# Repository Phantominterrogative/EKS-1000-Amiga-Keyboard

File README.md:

# EKS-1000-Amiga-Keyboard
A new PCB for those who like the Amiga A1000 keyboard.
This is an open source design. Feel free to download and import into KiCAD or EagleCAD for your own personal use.

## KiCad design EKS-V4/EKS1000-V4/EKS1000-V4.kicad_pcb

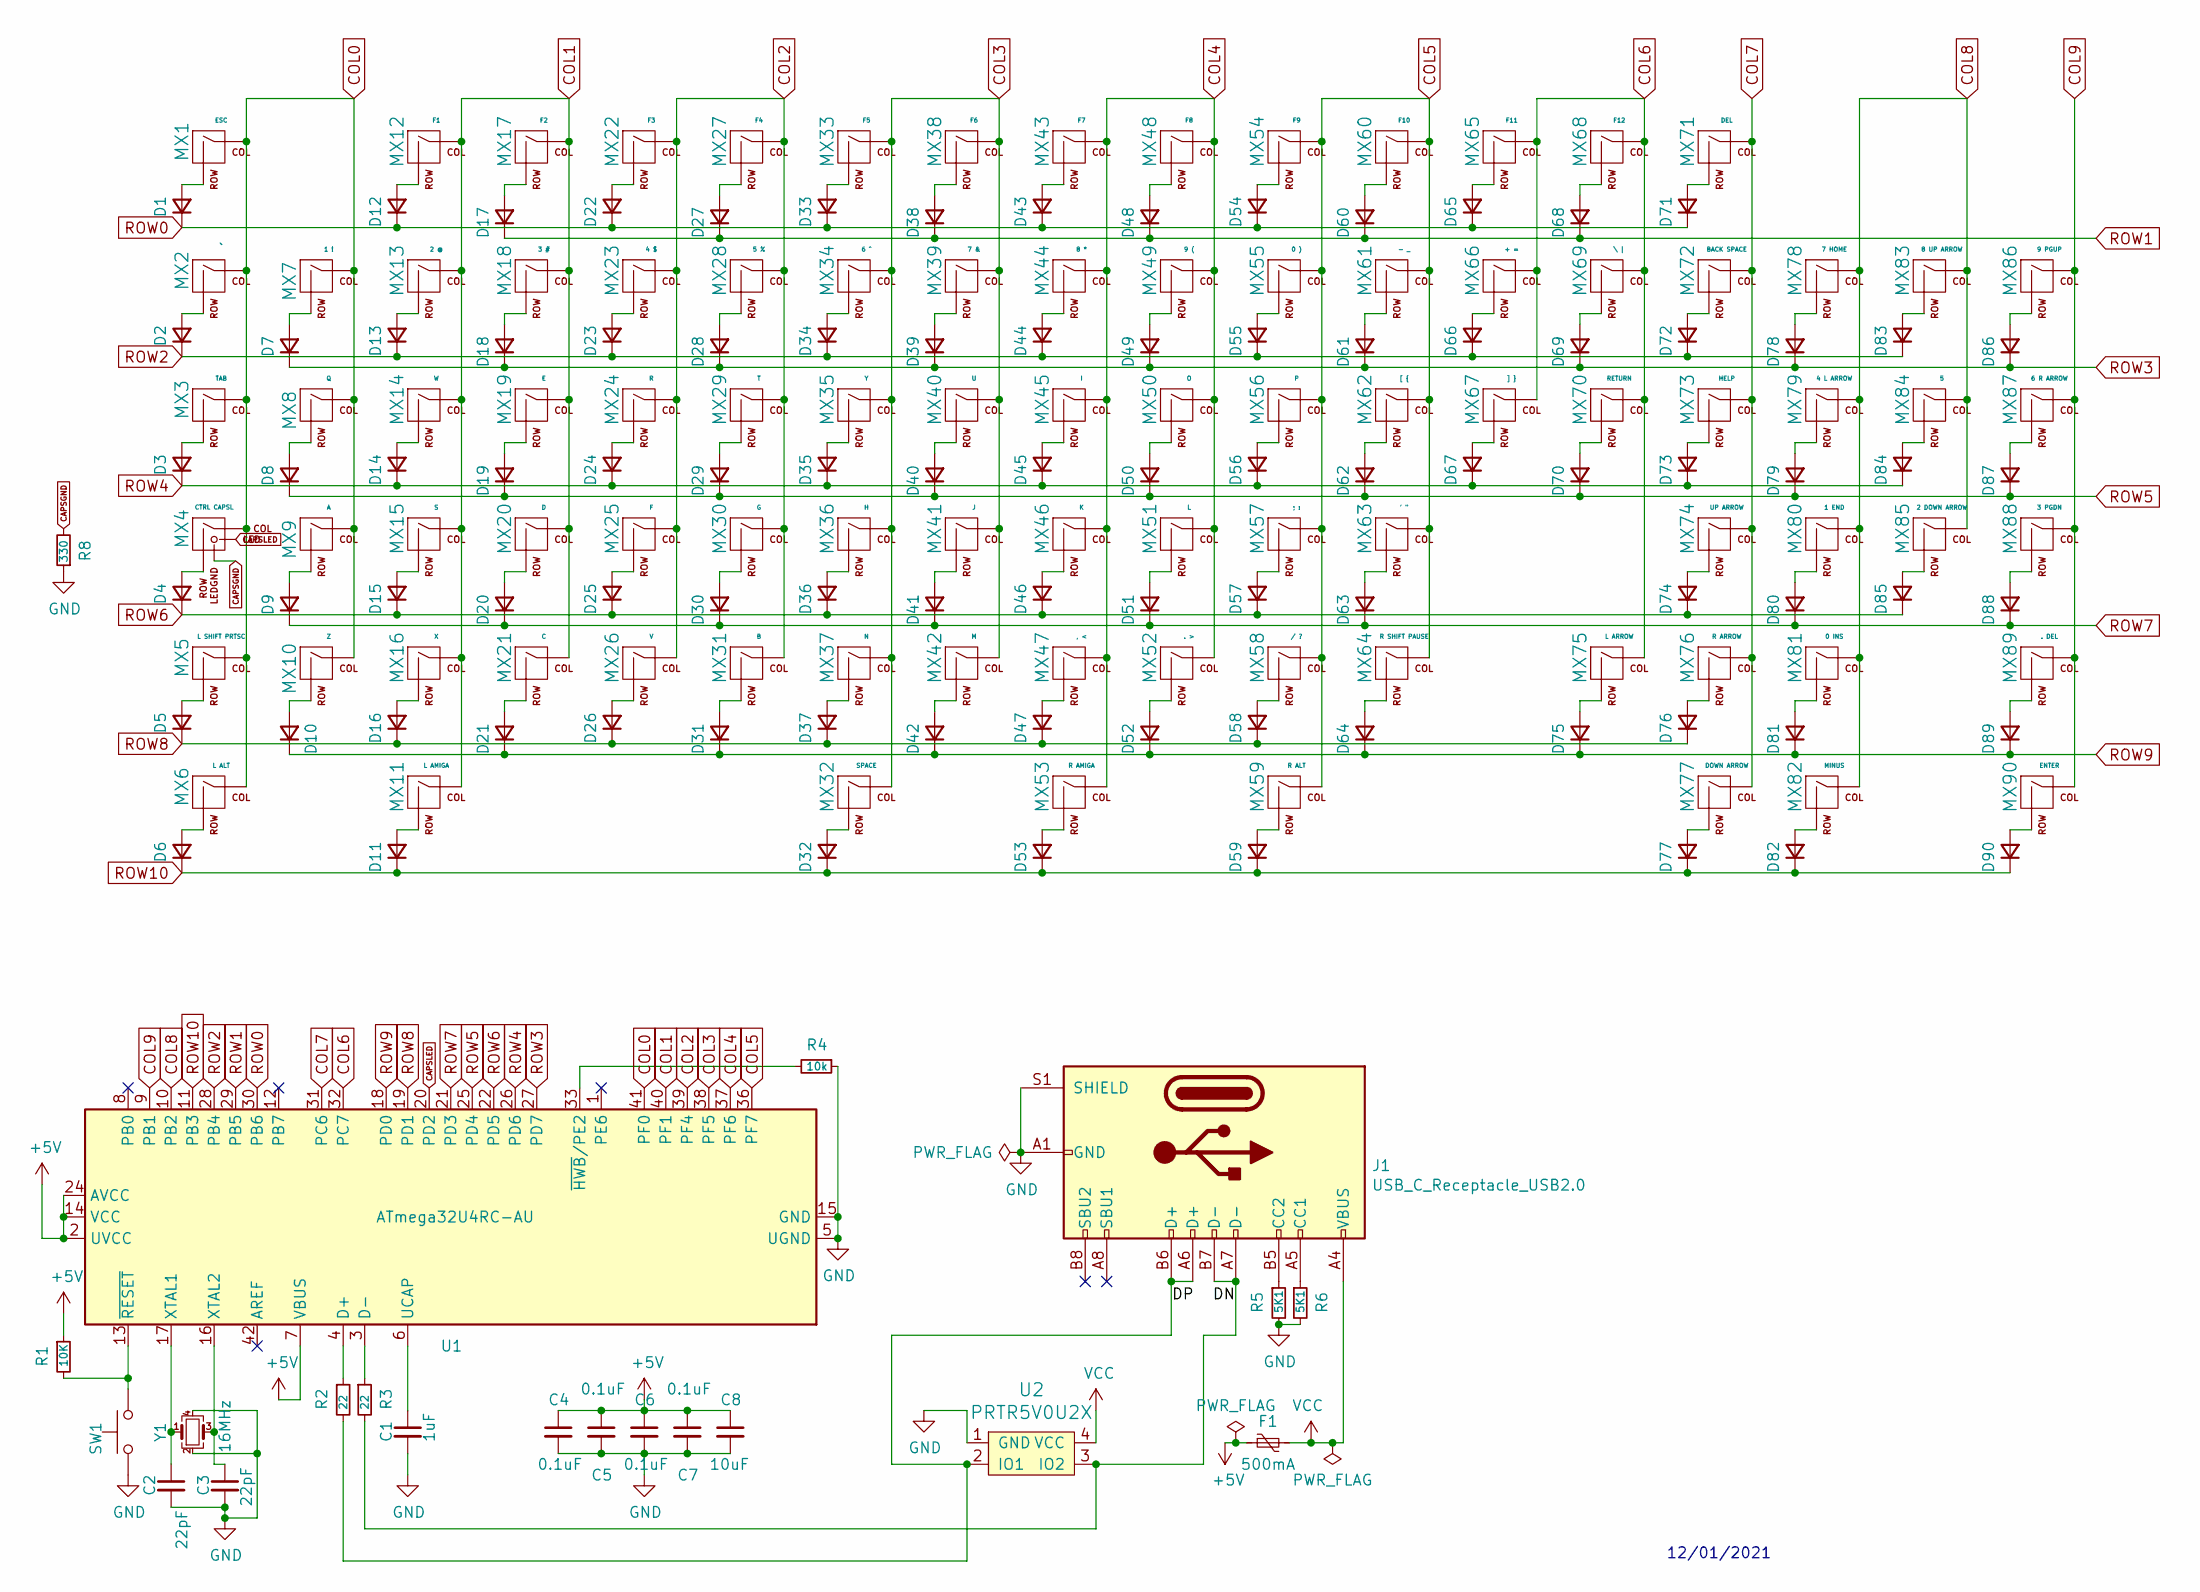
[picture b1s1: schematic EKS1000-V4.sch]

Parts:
C1: 1uF; C_0805_2012Metric
C2, C3: 22pF; C_0805_2012Metric
C4, C5, C6, C7: 0.1uF; C_0805_2012Metric
C8: 10uF; C_0805_2012Metric
D1, D2, D3, D4, D5, D6, D7, D8, D9, D10, D11, D12, D13, D14, D15, D16, D17, D18, D19, D20, D21, D22, D23, D24, D25, D26, D27, D28, D29, D30, D31, D32, D33, D34, D35, D36, D37, D38, D39, D40, D41, D42, D43, D44, D45, D46, D47, D48, D49, D50, D51, D52, D53, D54, D55, D56, D57, D58, D59, D60, D61, D62, D63, D64, D65, D66, D67, D68, D69, D70, D71, D72, D73, D74, D75, D76, D77, D78, D79, D80, D81, D82, D83, D84, D85, D86, D87, D88, D89, D90: D_Small; D_SOD-123
F1: 500mA; Fuse_1206_3216Metric
J1: USB_C_Receptacle_USB2.0; USB_C_Receptacle_HRO_TYPE-C-31-M-12
MX1: ESC; MXOnly-1U-NoLED
MX2: `~; MXOnly-1U-NoLED
MX3: TAB; MXOnly-1.5U-NoLED
MX4: CTRL CAPSL; MXOnly-1.75U-Rotated
MX5: L SHIFT PRTSC; MXOnly-2.25U-NoLED
MX6: L ALT; MXOnly-1.25U-NoLED
MX7: 1 !; MXOnly-1U-NoLED
MX8: Q; MXOnly-1U-NoLED
MX9: A; MXOnly-1U-NoLED
MX10: Z; MXOnly-1U-NoLED
MX11: L AMIGA; MXOnly-1.25U-NoLED
MX12: F1; MXOnly-1U-NoLED
MX13: 2 @; MXOnly-1U-NoLED
MX14: W; MXOnly-1U-NoLED
MX15: S; MXOnly-1U-NoLED
MX16: X; MXOnly-1U-NoLED
MX17: F2; MXOnly-1U-NoLED
MX18: 3 #; MXOnly-1U-NoLED
MX19: E; MXOnly-1U-NoLED
MX20: D; MXOnly-1U-NoLED
MX21: C; MXOnly-1U-NoLED
MX22: F3; MXOnly-1U-NoLED
MX23: 4 $; MXOnly-1U-NoLED
MX24: R; MXOnly-1U-NoLED
MX25: F; MXOnly-1U-NoLED
MX26: V; MXOnly-1U-NoLED
MX27: F4; MXOnly-1U-NoLED
MX28: 5 %; MXOnly-1U-NoLED
MX29: T; MXOnly-1U-NoLED
MX30: G; MXOnly-1U-NoLED
MX31: B; MXOnly-1U-NoLED
MX32: SPACE; MXOnly-7U-NoLED
MX33: F5; MXOnly-1U-NoLED
MX34: 6 ^; MXOnly-1U-NoLED
MX35: Y; MXOnly-1U-NoLED
MX36: H; MXOnly-1U-NoLED
MX37: N; MXOnly-1U-NoLED
MX38: F6; MXOnly-1U-NoLED
MX39: 7 &; MXOnly-1U-NoLED
MX40: U; MXOnly-1U-NoLED
MX41: J; MXOnly-1U-NoLED
MX42: M; MXOnly-1U-NoLED
MX43: F7; MXOnly-1U-NoLED
MX44: 8 *; MXOnly-1U-NoLED
MX45: I; MXOnly-1U-NoLED
MX46: K; MXOnly-1U-NoLED
MX47: , <; MXOnly-1U-NoLED
MX48: F8; MXOnly-1U-NoLED
MX49: 9 (; MXOnly-1U-NoLED
MX50: O; MXOnly-1U-NoLED
MX51: L; MXOnly-1U-NoLED
MX52: . >; MXOnly-1U-NoLED
MX53: R AMIGA; MXOnly-1.25U-NoLED
MX54: F9; MXOnly-1U-NoLED
MX55: 0 ); MXOnly-1U-NoLED
MX56: P; MXOnly-1U-NoLED
MX57: ; :; MXOnly-1U-NoLED
MX58: / ?; MXOnly-1U-NoLED
MX59: R ALT; MXOnly-1.25U-NoLED
MX60: F10; MXOnly-1U-NoLED
MX61: - _; MXOnly-1U-NoLED
MX62: [ {; MXOnly-1U-NoLED
MX63: ' \"; MXOnly-1U-NoLED
MX64: R SHIFT PAUSE; MXOnly-1.75U-NoLED
MX65: F11; MXOnly-1U-NoLED
MX66: + =; MXOnly-1U-NoLED
MX67: ] }; MXOnly-1U-NoLED
MX68: F12; MXOnly-1U-NoLED
MX69: \\ |; MXOnly-1U-NoLED
MX70: RETURN; MXOnly-sJL-NoLED
MX71: DEL; MXOnly-1U-NoLED
MX72: BACK SPACE; MXOnly-1.5U-NoLED
MX73: HELP; MXOnly-1U-NoLED
MX74: UP ARROW; MXOnly-1U-NoLED
MX75: L ARROW; MXOnly-1U-NoLED
MX76: R ARROW; MXOnly-1U-NoLED
MX77: DOWN ARROW; MXOnly-1U-NoLED
MX78: 7 HOME; MXOnly-1U-NoLED
MX79: 4 L ARROW; MXOnly-1U-NoLED
MX80: 1 END; MXOnly-1U-NoLED
MX81: 0 INS; MXOnly-2U-NoLED
MX82: MINUS; MXOnly-1U-NoLED
MX83: 8 UP ARROW; MXOnly-1U-NoLED
MX84: 5; MXOnly-1U-NoLED
MX85: 2 DOWN ARROW; MXOnly-1U-NoLED
MX86: 9 PGUP; MXOnly-1U-NoLED
MX87: 6 R ARROW; MXOnly-1U-NoLED
MX88: 3 PGDN; MXOnly-1U-NoLED
MX89: . DEL; MXOnly-1U-NoLED
MX90: ENTER; MXOnly-2U-NoLED
R1: 10K; R_0805_2012Metric
R2, R3: 22; R_0805_2012Metric
R4: 10k; R_0805_2012Metric
R5, R6: 5K1; R_0805_2012Metric
R8: 330; R_0805_2012Metric
SW1: SW_Push; SKQG-1155865
U1: ATmega32U4RC-AU; TQFP-44_10x10mm_P0.8mm
U2: PRTR5V0U2X; SOT143B
Y1: 16MHz; Crystal_SMD_3225-4Pin_3.2x2.5mm

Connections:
+5V: C4.1, C5.1, C6.1, C7.1, C8.1, F1.1, R1.1, U1.2 (UVCC), U1.7 (VBUS), U1.14 (VCC), U1.24 (AVCC), U1.34 (VCC), U1.44 (AVCC)
/DN: J1.A7 (D-), J1.B7 (D-), R3.2, U2.3 (IO2)
/DP: J1.A6 (D+), J1.B6 (D+), R2.2, U2.2 (IO1)
CAPSGND: MX4.4 (LEDGND), R8.2
CAPSLED: MX4.3 (LED), U1.20 (PD2)
COL0: MX1.1 (COL), MX2.1 (COL), MX3.1 (COL), MX4.1 (COL), MX5.1 (COL), MX6.1 (COL), MX7.1 (COL), MX8.1 (COL), MX9.1 (COL), MX10.1 (COL), U1.41 (PF0)
COL1: MX11.1 (COL), MX12.1 (COL), MX13.1 (COL), MX14.1 (COL), MX15.1 (COL), MX16.1 (COL), MX17.1 (COL), MX18.1 (COL), MX19.1 (COL), MX20.1 (COL), MX21.1 (COL), U1.40 (PF1)
COL2: MX22.1 (COL), MX23.1 (COL), MX24.1 (COL), MX25.1 (COL), MX26.1 (COL), MX27.1 (COL), MX28.1 (COL), MX29.1 (COL), MX30.1 (COL), MX31.1 (COL), U1.39 (PF4)
COL3: MX32.1 (COL), MX33.1 (COL), MX34.1 (COL), MX35.1 (COL), MX36.1 (COL), MX37.1 (COL), MX38.1 (COL), MX39.1 (COL), MX40.1 (COL), MX41.1 (COL), MX42.1 (COL), U1.38 (PF5)
COL4: MX43.1 (COL), MX44.1 (COL), MX45.1 (COL), MX46.1 (COL), MX47.1 (COL), MX48.1 (COL), MX49.1 (COL), MX50.1 (COL), MX51.1 (COL), MX52.1 (COL), MX53.1 (COL), U1.37 (PF6)
COL5: MX54.1 (COL), MX55.1 (COL), MX56.1 (COL), MX57.1 (COL), MX58.1 (COL), MX59.1 (COL), MX60.1 (COL), MX61.1 (COL), MX62.1 (COL), MX63.1 (COL), MX64.1 (COL), U1.36 (PF7)
COL6: MX65.1 (COL), MX66.1 (COL), MX67.1 (COL), MX68.1 (COL), MX69.1 (COL), MX70.1 (COL), MX75.1 (COL), U1.32 (PC7)
COL7: MX71.1 (COL), MX72.1 (COL), MX73.1 (COL), MX74.1 (COL), MX76.1 (COL), MX77.1 (COL), U1.31 (PC6)
COL8: MX78.1 (COL), MX79.1 (COL), MX80.1 (COL), MX81.1 (COL), MX82.1 (COL), MX83.1 (COL), MX84.1 (COL), MX85.1 (COL), U1.10 (PB2)
COL9: MX86.1 (COL), MX87.1 (COL), MX88.1 (COL), MX89.1 (COL), MX90.1 (COL), U1.9 (PB1)
GND: C1.2, C2.2, C3.2, C4.2, C5.2, C6.2, C7.2, C8.2, J1.A1 (GND), J1.A12 (GND), J1.B1 (GND), J1.B12 (GND), J1.S1 (SHIELD), R4.1, R5.2, R6.2, R8.1, SW1.1, U1.5 (UGND), U1.15 (GND), U1.23 (GND), U1.35 (GND), U1.43 (GND), U2.1 (GND), Y1.2, Y1.4
unnamed: C1.1, U1.6 (UCAP)
unnamed: C2.1, U1.17 (XTAL1), Y1.1
unnamed: C3.1, U1.16 (XTAL2), Y1.3
unnamed: D1.2 (A), MX1.2 (ROW)
unnamed: D2.2 (A), MX2.2 (ROW)
unnamed: D3.2 (A), MX3.2 (ROW)
unnamed: D4.2 (A), MX4.2 (ROW)
unnamed: D5.2 (A), MX5.2 (ROW)
unnamed: D6.2 (A), MX6.2 (ROW)
unnamed: D7.2 (A), MX7.2 (ROW)
unnamed: D8.2 (A), MX8.2 (ROW)
unnamed: D9.2 (A), MX9.2 (ROW)
unnamed: D10.2 (A), MX10.2 (ROW)
unnamed: D11.2 (A), MX11.2 (ROW)
unnamed: D12.2 (A), MX12.2 (ROW)
unnamed: D13.2 (A), MX13.2 (ROW)
unnamed: D14.2 (A), MX14.2 (ROW)
unnamed: D15.2 (A), MX15.2 (ROW)
unnamed: D16.2 (A), MX16.2 (ROW)
unnamed: D17.2 (A), MX17.2 (ROW)
unnamed: D18.2 (A), MX18.2 (ROW)
unnamed: D19.2 (A), MX19.2 (ROW)
unnamed: D20.2 (A), MX20.2 (ROW)
unnamed: D21.2 (A), MX21.2 (ROW)
unnamed: D22.2 (A), MX22.2 (ROW)
unnamed: D23.2 (A), MX23.2 (ROW)
unnamed: D24.2 (A), MX24.2 (ROW)
unnamed: D25.2 (A), MX25.2 (ROW)
unnamed: D26.2 (A), MX26.2 (ROW)
unnamed: D27.2 (A), MX27.2 (ROW)
unnamed: D28.2 (A), MX28.2 (ROW)
unnamed: D29.2 (A), MX29.2 (ROW)
unnamed: D30.2 (A), MX30.2 (ROW)
unnamed: D31.2 (A), MX31.2 (ROW)
unnamed: D32.2 (A), MX32.2 (ROW)
unnamed: D33.2 (A), MX33.2 (ROW)
unnamed: D34.2 (A), MX34.2 (ROW)
unnamed: D35.2 (A), MX35.2 (ROW)
unnamed: D36.2 (A), MX36.2 (ROW)
unnamed: D37.2 (A), MX37.2 (ROW)
unnamed: D38.2 (A), MX38.2 (ROW)
unnamed: D39.2 (A), MX39.2 (ROW)
unnamed: D40.2 (A), MX40.2 (ROW)
unnamed: D41.2 (A), MX41.2 (ROW)
unnamed: D42.2 (A), MX42.2 (ROW)
unnamed: D43.2 (A), MX43.2 (ROW)
unnamed: D44.2 (A), MX44.2 (ROW)
unnamed: D45.2 (A), MX45.2 (ROW)
unnamed: D46.2 (A), MX46.2 (ROW)
unnamed: D47.2 (A), MX47.2 (ROW)
unnamed: D48.2 (A), MX48.2 (ROW)
unnamed: D49.2 (A), MX49.2 (ROW)
unnamed: D50.2 (A), MX50.2 (ROW)
unnamed: D51.2 (A), MX51.2 (ROW)
unnamed: D52.2 (A), MX52.2 (ROW)
unnamed: D53.2 (A), MX53.2 (ROW)
unnamed: D54.2 (A), MX54.2 (ROW)
unnamed: D55.2 (A), MX55.2 (ROW)
unnamed: D56.2 (A), MX56.2 (ROW)
unnamed: D57.2 (A), MX57.2 (ROW)
unnamed: D58.2 (A), MX58.2 (ROW)
unnamed: D59.2 (A), MX59.2 (ROW)
unnamed: D60.2 (A), MX60.2 (ROW)
unnamed: D61.2 (A), MX61.2 (ROW)
unnamed: D62.2 (A), MX62.2 (ROW)
unnamed: D63.2 (A), MX63.2 (ROW)
unnamed: D64.2 (A), MX64.2 (ROW)
unnamed: D65.2 (A), MX65.2 (ROW)
unnamed: D66.2 (A), MX66.2 (ROW)
unnamed: D67.2 (A), MX67.2 (ROW)
unnamed: D68.2 (A), MX68.2 (ROW)
unnamed: D69.2 (A), MX69.2 (ROW)
unnamed: D70.2 (A), MX70.2 (ROW)
unnamed: D71.2 (A), MX71.2 (ROW)
unnamed: D72.2 (A), MX72.2 (ROW)
unnamed: D73.2 (A), MX73.2 (ROW)
unnamed: D74.2 (A), MX74.2 (ROW)
unnamed: D75.2 (A), MX75.2 (ROW)
unnamed: D76.2 (A), MX76.2 (ROW)
unnamed: D77.2 (A), MX77.2 (ROW)
unnamed: D78.2 (A), MX78.2 (ROW)
unnamed: D79.2 (A), MX79.2 (ROW)
unnamed: D80.2 (A), MX80.2 (ROW)
unnamed: D81.2 (A), MX81.2 (ROW)
unnamed: D82.2 (A), MX82.2 (ROW)
unnamed: D83.2 (A), MX83.2 (ROW)
unnamed: D84.2 (A), MX84.2 (ROW)
unnamed: D85.2 (A), MX85.2 (ROW)
unnamed: D86.2 (A), MX86.2 (ROW)
unnamed: D87.2 (A), MX87.2 (ROW)
unnamed: D88.2 (A), MX88.2 (ROW)
unnamed: D89.2 (A), MX89.2 (ROW)
unnamed: D90.2 (A), MX90.2 (ROW)
unnamed: J1.A5 (CC1), R6.1
unnamed: J1.B5 (CC2), R5.1
unnamed: R1.2, SW1.2, U1.13 (~RESET)
unnamed: R2.1, U1.4 (D+)
unnamed: R3.1, U1.3 (D-)
unnamed: R4.2, U1.33 (~HWB~/PE2)
ROW0: D1.1 (K), D12.1 (K), D22.1 (K), D33.1 (K), D43.1 (K), D54.1 (K), D65.1 (K), D71.1 (K), U1.30 (PB6)
ROW1: D17.1 (K), D27.1 (K), D38.1 (K), D48.1 (K), D60.1 (K), D68.1 (K), U1.29 (PB5)
ROW2: D2.1 (K), D13.1 (K), D23.1 (K), D34.1 (K), D44.1 (K), D55.1 (K), D66.1 (K), D72.1 (K), D83.1 (K), U1.28 (PB4)
ROW3: D7.1 (K), D18.1 (K), D28.1 (K), D39.1 (K), D49.1 (K), D61.1 (K), D69.1 (K), D78.1 (K), D86.1 (K), U1.27 (PD7)
ROW4: D3.1 (K), D14.1 (K), D24.1 (K), D35.1 (K), D45.1 (K), D56.1 (K), D67.1 (K), D73.1 (K), D84.1 (K), U1.26 (PD6)
ROW5: D8.1 (K), D19.1 (K), D29.1 (K), D40.1 (K), D50.1 (K), D62.1 (K), D70.1 (K), D79.1 (K), D87.1 (K), U1.25 (PD4)
ROW6: D4.1 (K), D15.1 (K), D25.1 (K), D36.1 (K), D46.1 (K), D57.1 (K), D74.1 (K), D85.1 (K), U1.22 (PD5)
ROW7: D9.1 (K), D20.1 (K), D30.1 (K), D41.1 (K), D51.1 (K), D63.1 (K), D80.1 (K), D88.1 (K), U1.21 (PD3)
ROW8: D5.1 (K), D16.1 (K), D26.1 (K), D37.1 (K), D47.1 (K), D58.1 (K), D76.1 (K), U1.19 (PD1)
ROW9: D10.1 (K), D21.1 (K), D31.1 (K), D42.1 (K), D52.1 (K), D64.1 (K), D75.1 (K), D81.1 (K), D89.1 (K), U1.18 (PD0)
ROW10: D6.1 (K), D11.1 (K), D32.1 (K), D53.1 (K), D59.1 (K), D77.1 (K), D82.1 (K), D90.1 (K), U1.11 (PB3)
VCC: F1.2, J1.A4 (VBUS), J1.A9 (VBUS), J1.B4 (VBUS), J1.B9 (VBUS), U2.4 (VCC)

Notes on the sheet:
12/01/2021

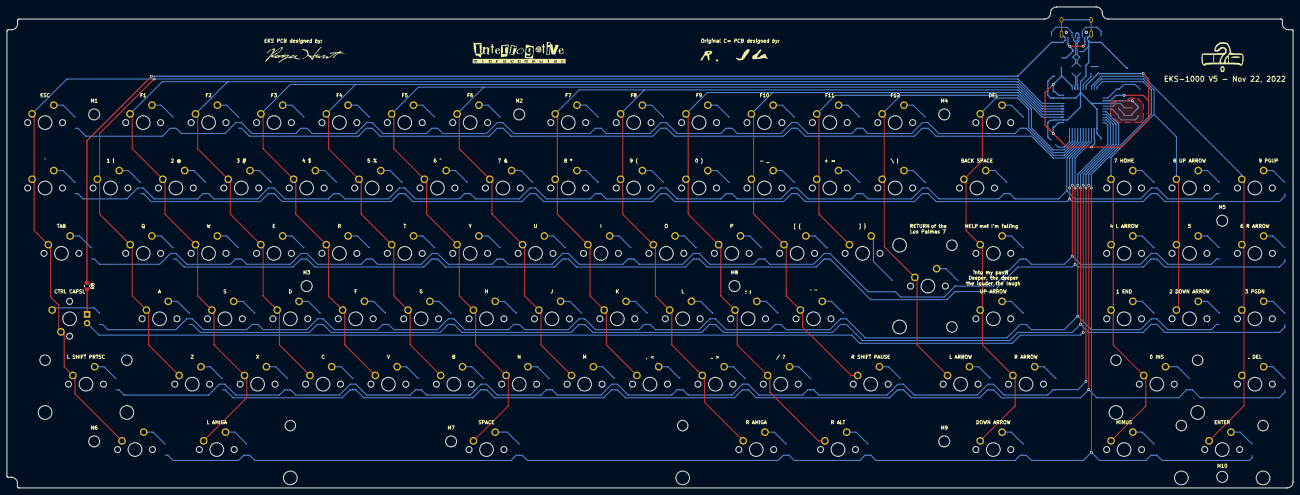
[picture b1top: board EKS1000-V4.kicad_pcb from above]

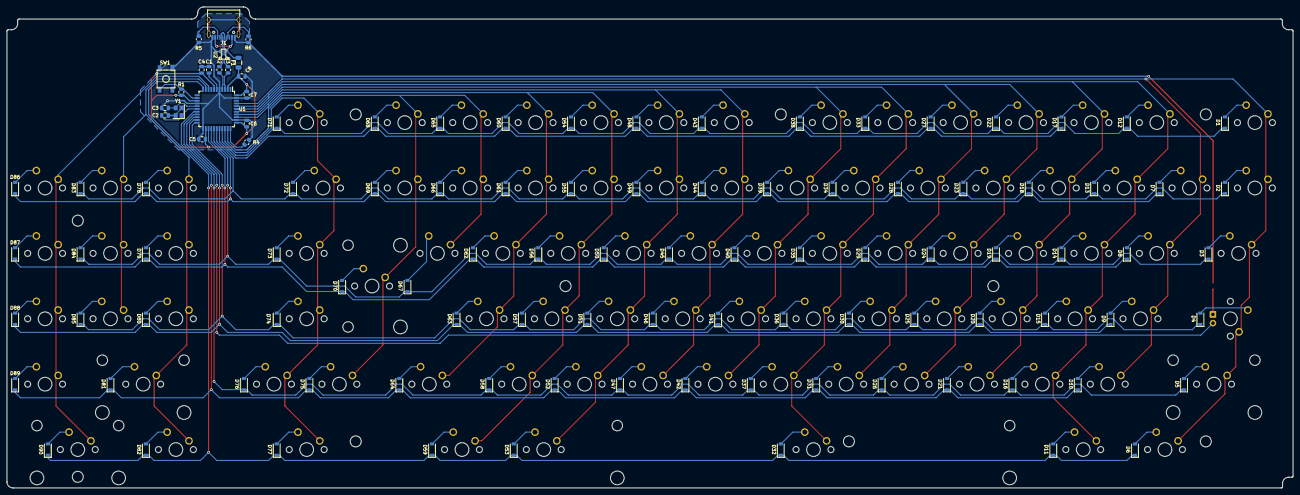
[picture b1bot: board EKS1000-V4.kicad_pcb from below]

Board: 2 copper layers, 374.6 x 140.1 mm, 215 parts (110 on the bottom side), 127 nets.

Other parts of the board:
G1: LOGO; Interrogative
G2: LOGO; MySig
G4: LOGO; RIda
G4#2: LOGO; IPrefs
M1, M2, M3, M4, M5, M6, M7, M8, M9, M10: MountingHole_3.2mm_M3

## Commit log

2022-11-22 Add files via upload
    I have cleaned up the repository of old files. The new files are for the V4 EKS1000.
